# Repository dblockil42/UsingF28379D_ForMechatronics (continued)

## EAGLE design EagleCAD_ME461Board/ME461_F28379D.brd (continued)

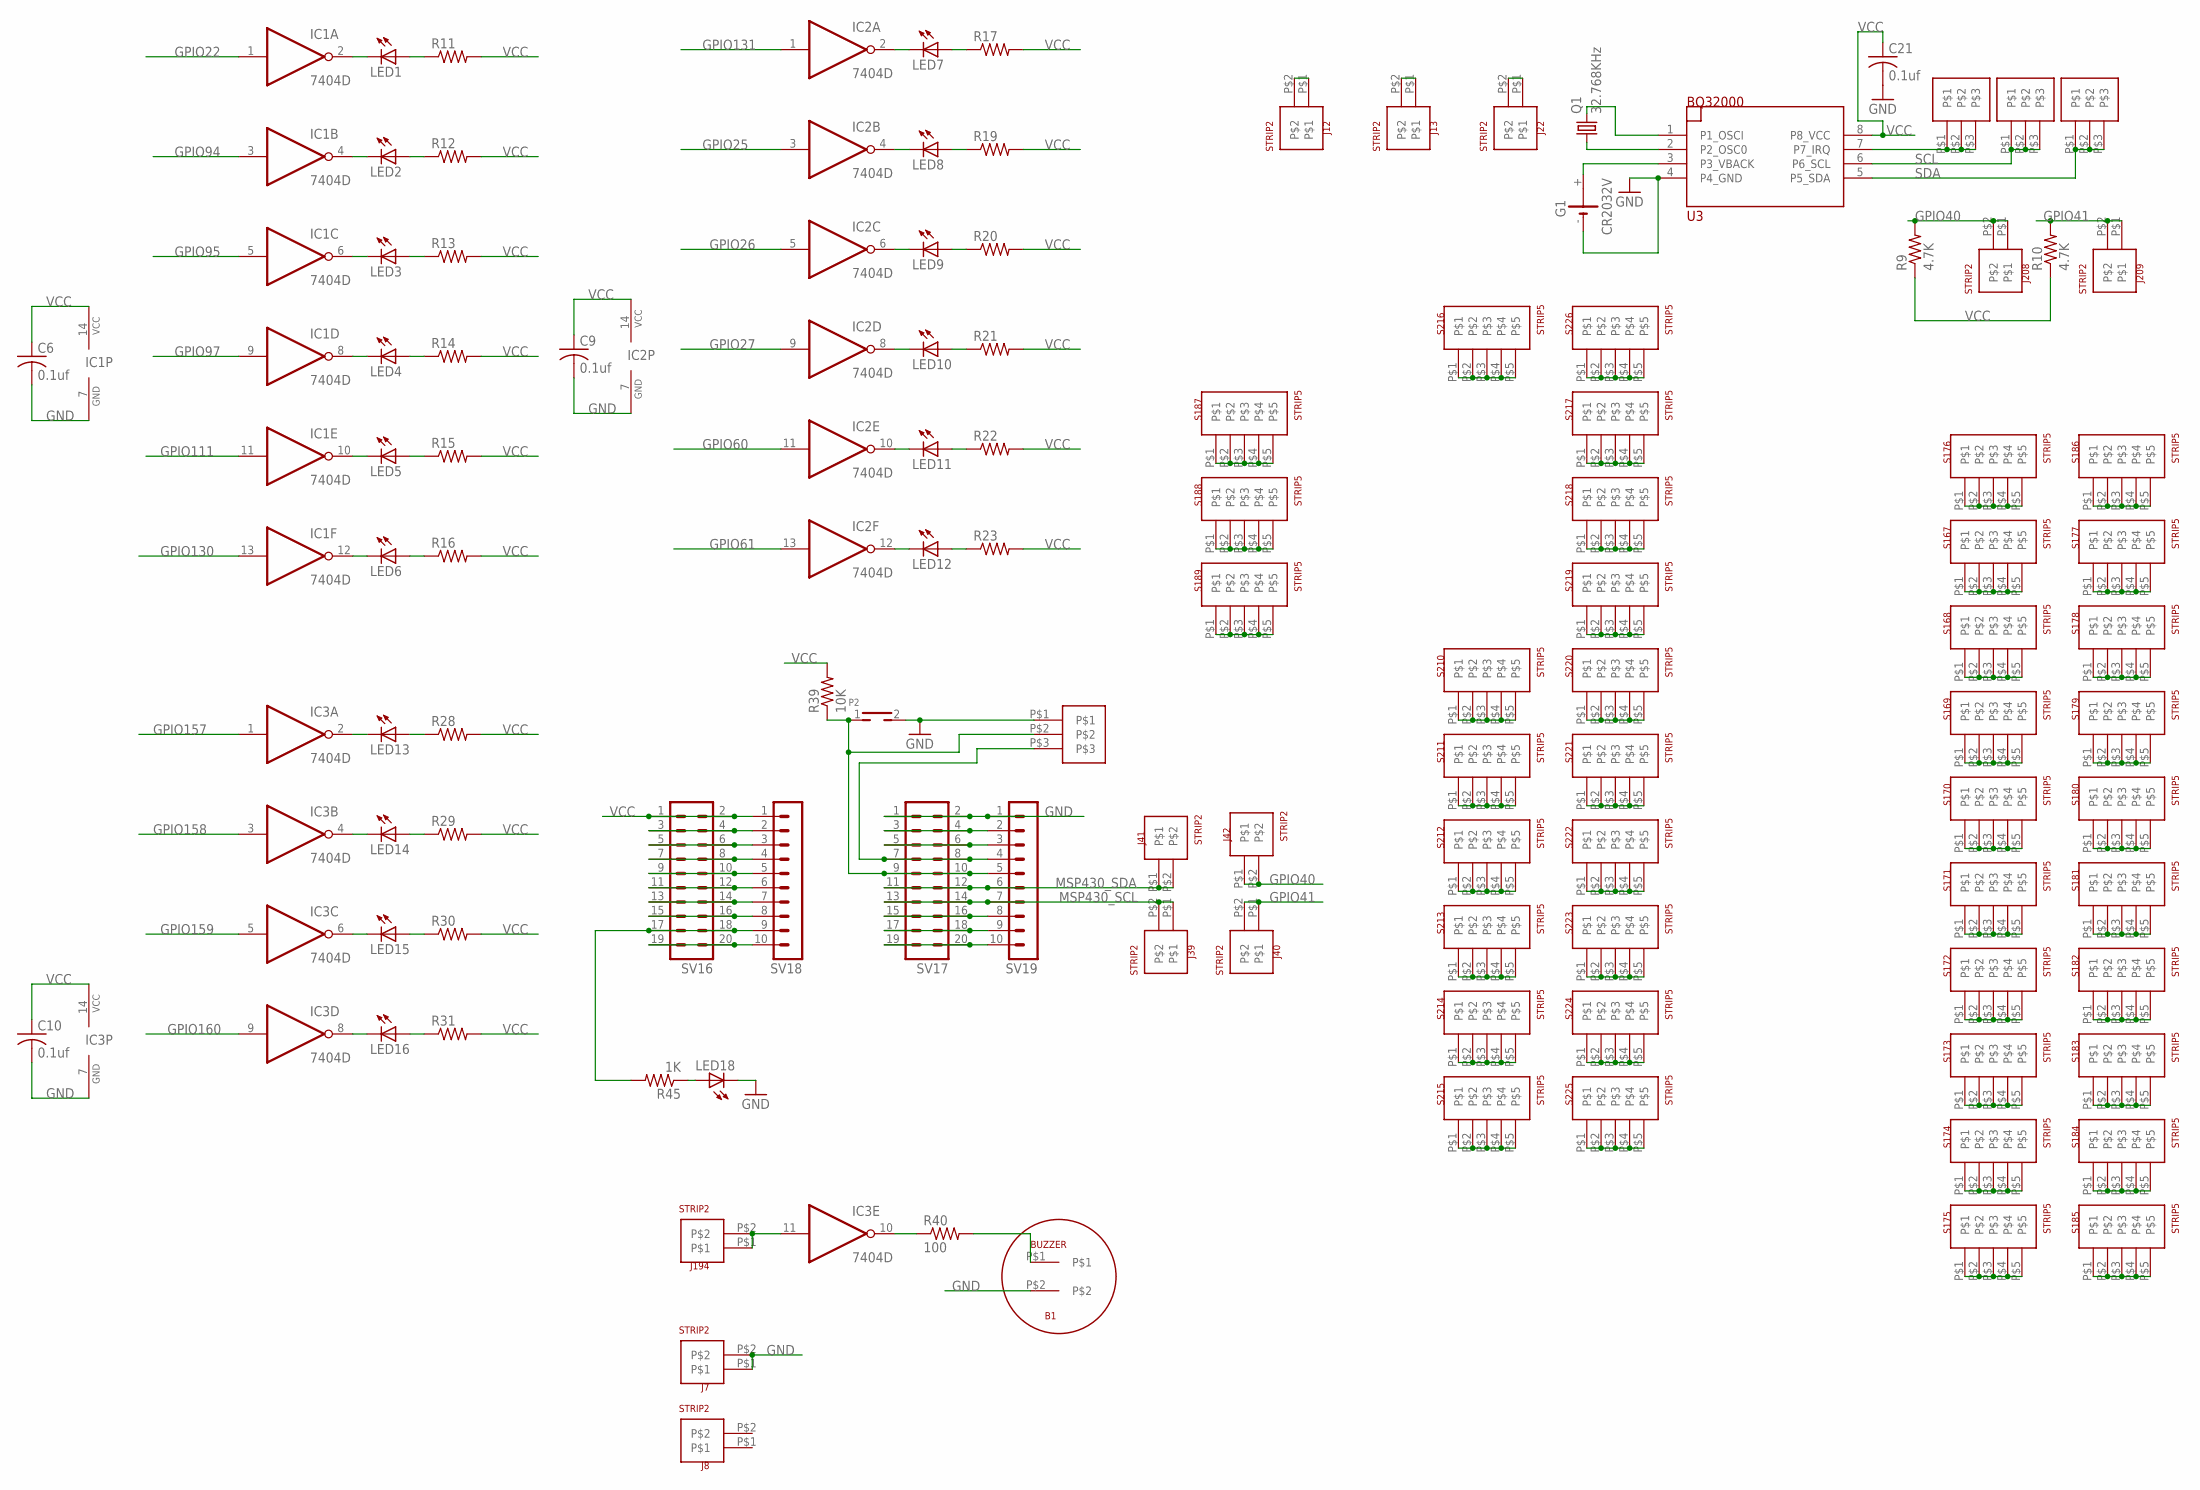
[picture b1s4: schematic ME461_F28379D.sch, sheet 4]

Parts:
B1: BUZZER
C6, C9, C10, C21: 0.1uf; C1206
G1: CR2032V
IC1, IC2, IC3: 7404D; SO14
J1, J2, J3, J43: STRIP3
J7, J8, J12, J13, J22, J39, J40, J41, J42, J194, J208, J209: STRIP2
LED1, LED2, LED3, LED4, LED5, LED6, LED7, LED8, LED9, LED10, LED11, LED12, LED13, LED14, LED15, LED16, LED18: LEDCHIPLED_1206; CHIPLED_1206
P2: TH_PUSHBOTTON; TH_PUSHBUTTON
Q1: 32.768KHz; TC26H
R9, R10: 4.7K; R1206
R11, R12, R13, R14, R15, R16, R17, R19, R20, R21, R22, R23, R28, R29, R30, R31: R-US_R1206; R1206
R39: 10K; R1206
R40: 100; R1206
R45: 1K; R1206
S167, S168, S169, S170, S171, S172, S173, S174, S175, S176, S177, S178, S179, S180, S181, S182, S183, S184, S185, S186, S187, S188, S189, S210, S211, S212, S213, S214, S215, S216, S217, S218, S219, S220, S221, S222, S223, S224, S225, S226: STRIP5
SV16, SV17: MA10-2
SV18, SV19: MA10-1
U3: BQ32000; SO08

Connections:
GND: B1.P$2, C6.2, C9.2, C10.2, C21.2, G1.-, IC1.7 (GND), IC2.7 (GND), IC3.7 (GND), J7.P$1, J7.P$2, J43.P$1, LED18.C, P2.2, SV17.1, SV17.2, SV19.1, U3.4 (P4_GND); also elsewhere on the board
GPIO22: IC1.1 (I); also elsewhere on the board
GPIO25: IC2.3 (I); also elsewhere on the board
GPIO26: IC2.5 (I); also elsewhere on the board
GPIO27: IC2.9 (I); also elsewhere on the board
GPIO40: J42.P$1, J42.P$2, J208.P$1, J208.P$2, R9.2; also elsewhere on the board
GPIO41: J40.P$1, J40.P$2, J209.P$1, J209.P$2, R10.2; also elsewhere on the board
GPIO60: IC2.11 (I); also elsewhere on the board
GPIO61: IC2.13 (I); also elsewhere on the board
GPIO94: IC1.3 (I); also elsewhere on the board
GPIO95: IC1.5 (I); also elsewhere on the board
GPIO97: IC1.9 (I); also elsewhere on the board
GPIO111: IC1.11 (I); also elsewhere on the board
GPIO130: IC1.13 (I); also elsewhere on the board
GPIO131: IC2.1 (I); also elsewhere on the board
GPIO157: IC3.1 (I); also elsewhere on the board
GPIO158: IC3.3 (I); also elsewhere on the board
GPIO159: IC3.5 (I); also elsewhere on the board
GPIO160: IC3.9 (I); also elsewhere on the board
MSP430_SCL: J39.P$1, J39.P$2, SV17.13, SV17.14, SV19.7
MSP430_SDA: J41.P$1, J41.P$2, SV17.11, SV17.12, SV19.6
unnamed: J12.P$1, J12.P$2
unnamed: J13.P$1, J13.P$2
unnamed: J22.P$1, J22.P$2
unnamed: R45.2, SV16.17, SV16.18, SV18.9
unnamed: SV16.3, SV16.4, SV18.2
unnamed: SV16.5, SV16.6, SV18.3
unnamed: SV16.7, SV16.8, SV18.4
unnamed: SV16.9, SV16.10, SV18.5
unnamed: SV16.11, SV16.12, SV18.6
unnamed: SV16.13, SV16.14, SV18.7
unnamed: SV16.15, SV16.16, SV18.8
unnamed: LED18.A, R45.1
unnamed: SV16.19, SV16.20, SV18.10
unnamed: SV17.3, SV17.4, SV19.2
unnamed: SV17.5, SV17.6, SV19.3
unnamed: J43.P$3, SV17.7, SV17.8, SV19.4
unnamed: SV17.15, SV17.16, SV19.8
unnamed: SV17.17, SV17.18, SV19.9
unnamed: SV17.19, SV17.20, SV19.10
unnamed: J43.P$2, P2.1, R39.1, SV17.9, SV17.10, SV19.5
unnamed: IC3.10 (O), R40.1
unnamed: B1.P$1, R40.2
unnamed: Q1.1, U3.2 (P2_OSC0)
unnamed: Q1.2, U3.1 (P1_OSCI)
unnamed: J1.P$1, J1.P$2, J1.P$3, U3.7 (P7_IRQ)
unnamed: G1.+, U3.3 (P3_VBACK)
unnamed: IC2.2 (O), LED7.C
unnamed: LED7.A, R17.1
unnamed: IC2.4 (O), LED8.C
unnamed: LED8.A, R19.1
unnamed: IC2.6 (O), LED9.C
unnamed: S167.P$1, S167.P$2, S167.P$3, S167.P$4, S167.P$5
unnamed: S168.P$1, S168.P$2, S168.P$3, S168.P$4, S168.P$5
unnamed: S169.P$1, S169.P$2, S169.P$3, S169.P$4, S169.P$5
unnamed: S170.P$1, S170.P$2, S170.P$3, S170.P$4, S170.P$5
unnamed: S171.P$1, S171.P$2, S171.P$3, S171.P$4, S171.P$5
unnamed: S172.P$1, S172.P$2, S172.P$3, S172.P$4, S172.P$5
unnamed: S173.P$1, S173.P$2, S173.P$3, S173.P$4, S173.P$5
unnamed: S174.P$1, S174.P$2, S174.P$3, S174.P$4, S174.P$5
unnamed: S175.P$1, S175.P$2, S175.P$3, S175.P$4, S175.P$5
unnamed: S176.P$1, S176.P$2, S176.P$3, S176.P$4, S176.P$5
unnamed: S177.P$1, S177.P$2, S177.P$3, S177.P$4, S177.P$5
unnamed: S178.P$1, S178.P$2, S178.P$3, S178.P$4, S178.P$5
unnamed: S179.P$1, S179.P$2, S179.P$3, S179.P$4, S179.P$5
unnamed: S180.P$1, S180.P$2, S180.P$3, S180.P$4, S180.P$5
unnamed: S181.P$1, S181.P$2, S181.P$3, S181.P$4, S181.P$5
unnamed: S182.P$1, S182.P$2, S182.P$3, S182.P$4, S182.P$5
unnamed: S183.P$1, S183.P$2, S183.P$3, S183.P$4, S183.P$5
unnamed: S184.P$1, S184.P$2, S184.P$3, S184.P$4, S184.P$5
unnamed: S185.P$1, S185.P$2, S185.P$3, S185.P$4, S185.P$5
unnamed: S186.P$1, S186.P$2, S186.P$3, S186.P$4, S186.P$5
unnamed: S187.P$1, S187.P$2, S187.P$3, S187.P$4, S187.P$5
unnamed: S188.P$1, S188.P$2, S188.P$3, S188.P$4, S188.P$5
unnamed: S189.P$1, S189.P$2, S189.P$3, S189.P$4, S189.P$5
unnamed: S210.P$1, S210.P$2, S210.P$3, S210.P$4, S210.P$5
unnamed: S211.P$1, S211.P$2, S211.P$3, S211.P$4, S211.P$5
unnamed: S212.P$1, S212.P$2, S212.P$3, S212.P$4, S212.P$5
unnamed: S213.P$1, S213.P$2, S213.P$3, S213.P$4, S213.P$5
unnamed: S214.P$1, S214.P$2, S214.P$3, S214.P$4, S214.P$5
unnamed: S215.P$1, S215.P$2, S215.P$3, S215.P$4, S215.P$5
unnamed: S216.P$1, S216.P$2, S216.P$3, S216.P$4, S216.P$5
unnamed: S217.P$1, S217.P$2, S217.P$3, S217.P$4, S217.P$5
unnamed: S218.P$1, S218.P$2, S218.P$3, S218.P$4, S218.P$5
unnamed: S219.P$1, S219.P$2, S219.P$3, S219.P$4, S219.P$5
unnamed: S220.P$1, S220.P$2, S220.P$3, S220.P$4, S220.P$5
unnamed: S221.P$1, S221.P$2, S221.P$3, S221.P$4, S221.P$5
unnamed: S222.P$1, S222.P$2, S222.P$3, S222.P$4, S222.P$5
unnamed: S223.P$1, S223.P$2, S223.P$3, S223.P$4, S223.P$5
unnamed: S224.P$1, S224.P$2, S224.P$3, S224.P$4, S224.P$5
unnamed: S225.P$1, S225.P$2, S225.P$3, S225.P$4, S225.P$5
unnamed: S226.P$1, S226.P$2, S226.P$3, S226.P$4, S226.P$5
unnamed: IC1.2 (O), LED1.C
unnamed: LED1.A, R11.1
unnamed: IC1.4 (O), LED2.C
unnamed: LED2.A, R12.1
unnamed: IC1.6 (O), LED3.C
unnamed: LED3.A, R13.1
unnamed: IC1.8 (O), LED4.C
unnamed: LED4.A, R14.1
unnamed: IC1.10 (O), LED5.C
unnamed: LED5.A, R15.1
unnamed: IC1.12 (O), LED6.C
unnamed: LED6.A, R16.1
unnamed: LED9.A, R20.1
unnamed: IC2.8 (O), LED10.C
unnamed: LED10.A, R21.1
unnamed: IC2.10 (O), LED11.C
unnamed: LED11.A, R22.1
unnamed: IC2.12 (O), LED12.C
unnamed: LED12.A, R23.1
unnamed: IC3.2 (O), LED13.C
unnamed: LED13.A, R28.1
unnamed: IC3.4 (O), LED14.C
unnamed: LED14.A, R29.1
unnamed: IC3.6 (O), LED15.C
unnamed: LED15.A, R30.1
unnamed: IC3.8 (O), LED16.C
unnamed: LED16.A, R31.1
unnamed: IC3.11 (I), J194.P$1, J194.P$2
SCL: J2.P$1, J2.P$2, J2.P$3, U3.6 (P6_SCL)
SDA: J3.P$1, J3.P$2, J3.P$3, U3.5 (P5_SDA)
VCC: C6.1, C9.1, C10.1, C21.1, IC1.14 (VCC), IC2.14 (VCC), IC3.14 (VCC), R9.1, R10.1, R11.2, R12.2, R13.2, R14.2, R15.2, R16.2, R17.2, R19.2, R20.2, R21.2, R22.2, R23.2, R28.2, R29.2, R30.2, R31.2, R39.2, SV16.1, SV16.2, SV18.1, U3.8 (P8_VCC); also elsewhere on the board

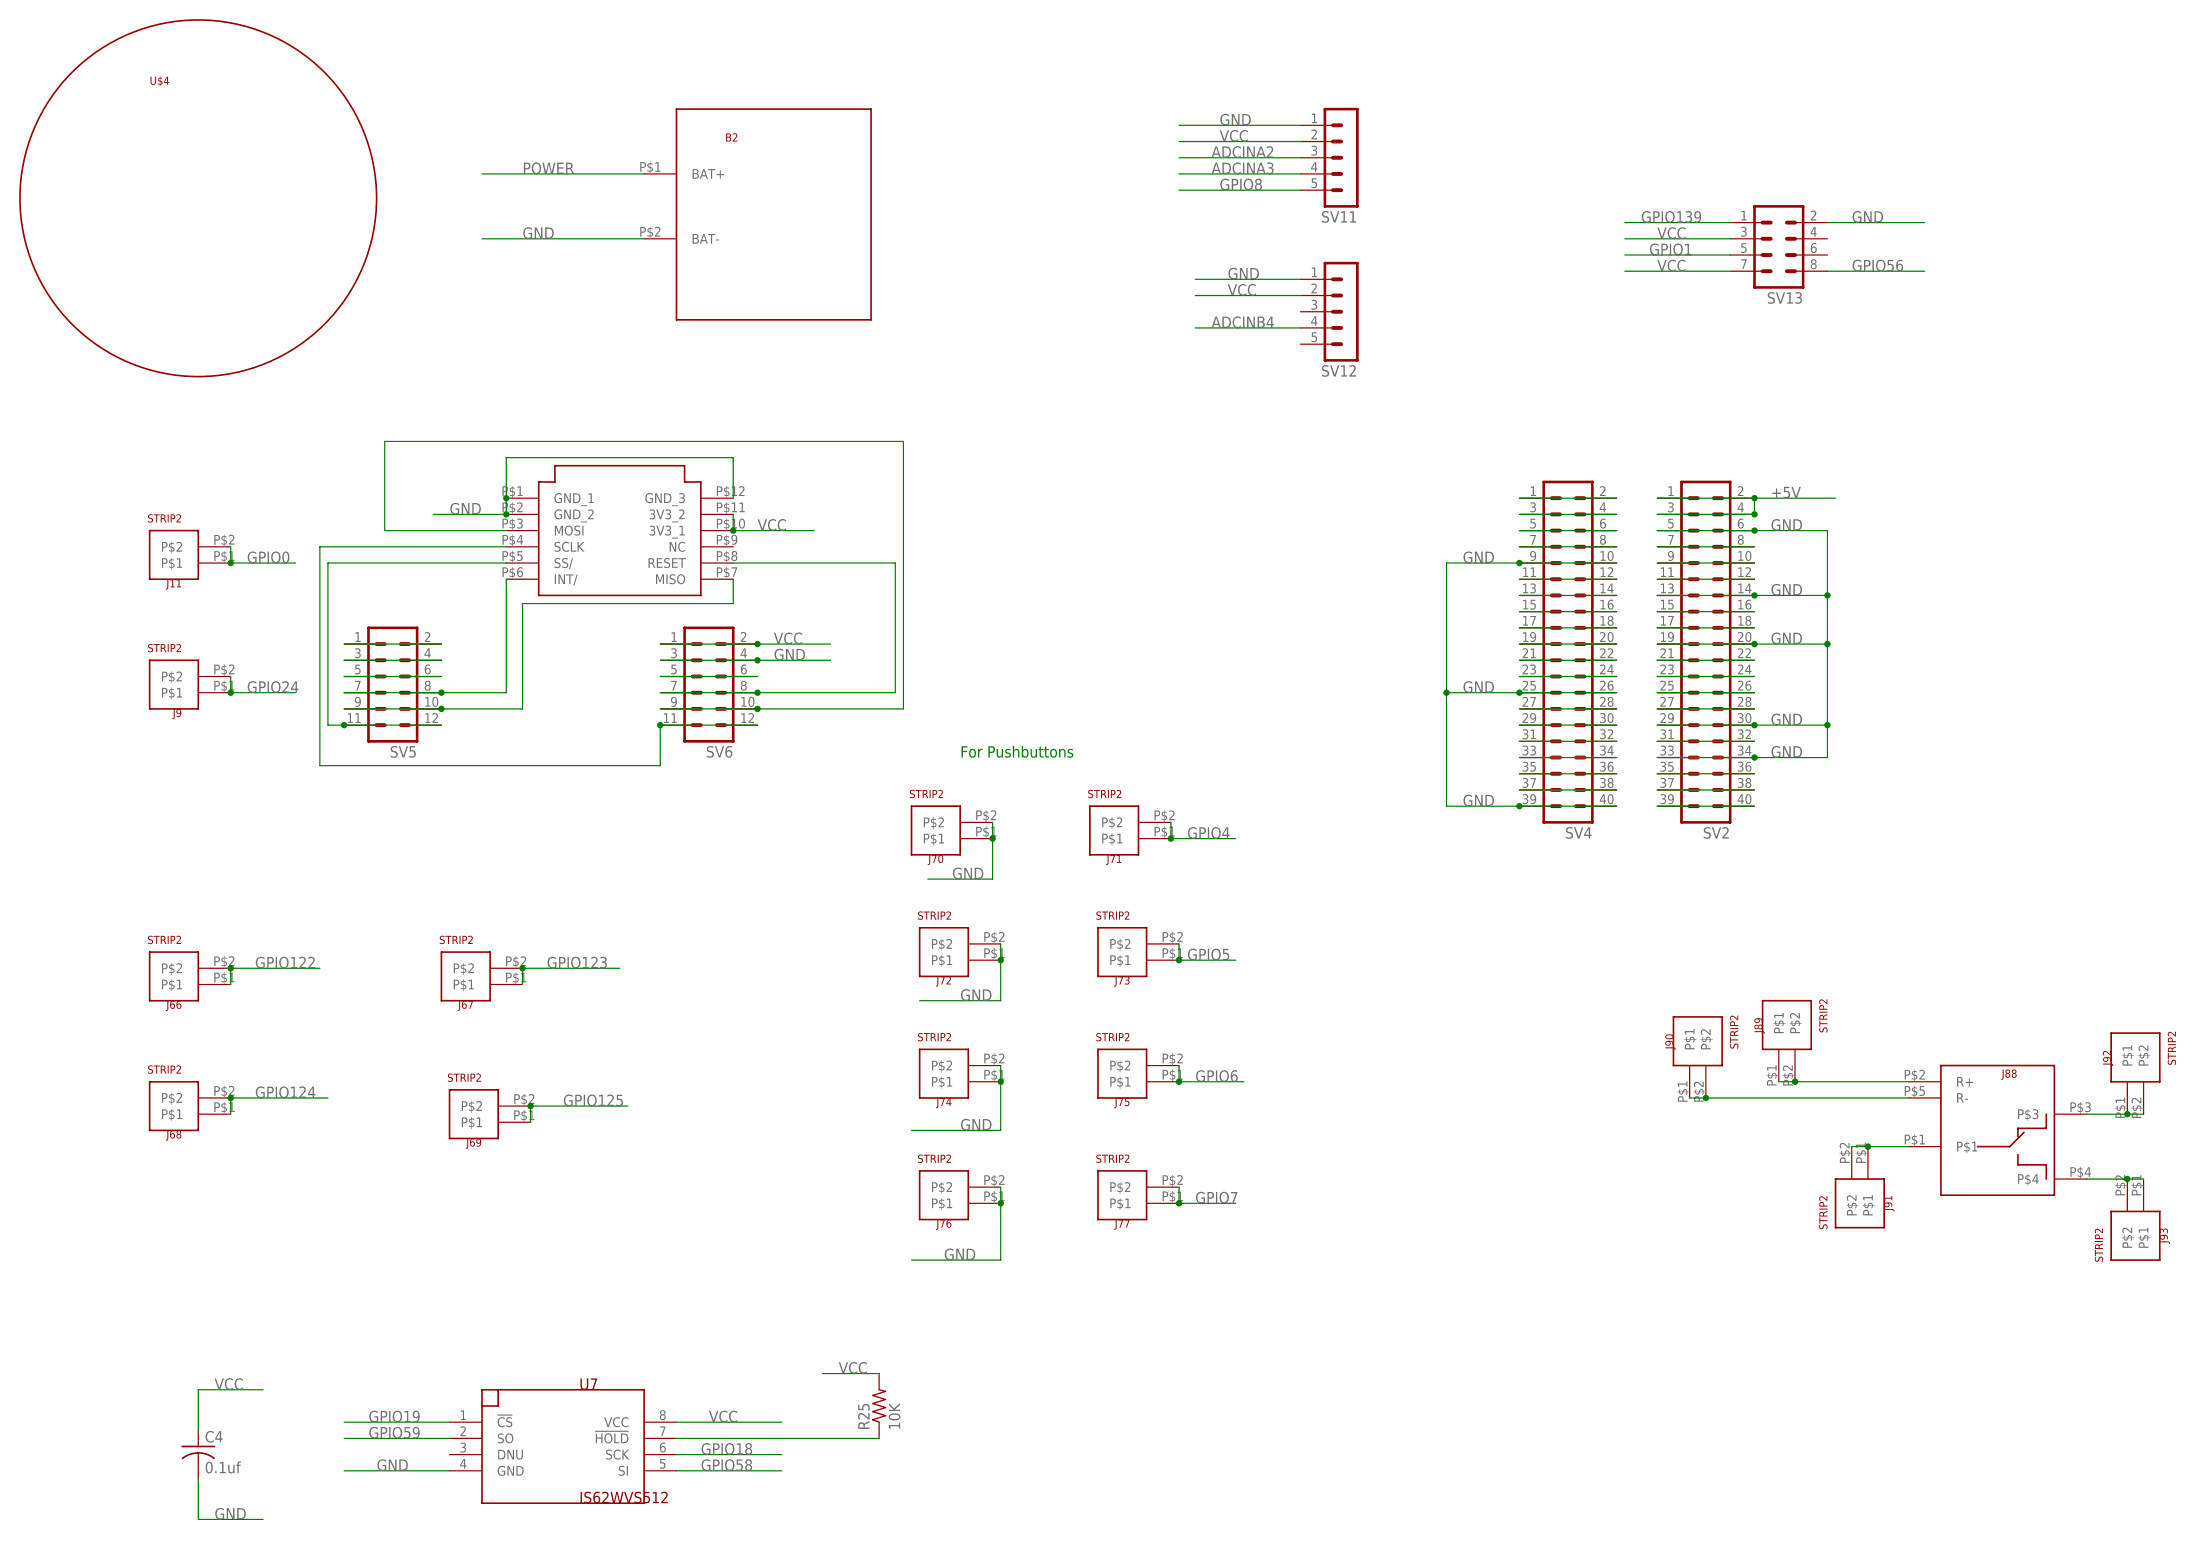
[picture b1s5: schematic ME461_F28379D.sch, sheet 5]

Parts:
B2: BATTERY_4AA_HOLDER
C4: 0.1uf; C1206
ETH1: USR_ES1_W5500
J9, J11, J66, J67, J68, J69, J70, J71, J72, J73, J74, J75, J76, J77, J89, J90, J91, J92, J93: STRIP2
J88: RELAY_JQC-3F_5V
R25: 10K; M1206
SV2, SV4: MA20-2
SV5, SV6: MA06-2
SV11, SV12: MA05-1
SV13: MA04-2
U7: IS62WVS512; SO08
U$4: CASTERWHEEL

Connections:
+5V: SV2.1, SV2.2, SV2.3, SV2.4; also elsewhere on the board
ADCINA2: SV11.3; also elsewhere on the board
ADCINA3: SV11.4; also elsewhere on the board
ADCINB4: SV12.4; also elsewhere on the board
GND: B2.P$2 (BAT-), C4.2, ETH1.P$1 (GND_1), ETH1.P$2 (GND_2), ETH1.P$12 (GND_3), J70.P$1, J70.P$2, J72.P$1, J72.P$2, J74.P$1, J74.P$2, J76.P$1, J76.P$2, SV2.5, SV2.6, SV2.13, SV2.14, SV2.19, SV2.20, SV2.29, SV2.30, SV2.33, SV2.34, SV4.9, SV4.10, SV4.25, SV4.26, SV4.39, SV4.40, SV6.3, SV6.4, SV11.1, SV12.1, SV13.2, U7.4 (GND); also elsewhere on the board
GPIO0: J11.P$1, J11.P$2; also elsewhere on the board
GPIO1: SV13.5; also elsewhere on the board
GPIO4: J71.P$1, J71.P$2; also elsewhere on the board
GPIO5: J73.P$1, J73.P$2; also elsewhere on the board
GPIO6: J75.P$1, J75.P$2; also elsewhere on the board
GPIO7: J77.P$1, J77.P$2; also elsewhere on the board
GPIO8: SV11.5; also elsewhere on the board
GPIO18: U7.6 (SCK); also elsewhere on the board
GPIO19: U7.1 (!CS); also elsewhere on the board
GPIO24: J9.P$1, J9.P$2; also elsewhere on the board
GPIO56: SV13.8; also elsewhere on the board
GPIO58: U7.5 (SI); also elsewhere on the board
GPIO59: U7.2 (SO); also elsewhere on the board
GPIO122: J66.P$1, J66.P$2; also elsewhere on the board
GPIO123: J67.P$1, J67.P$2; also elsewhere on the board
GPIO124: J68.P$1, J68.P$2; also elsewhere on the board
GPIO125: J69.P$1, J69.P$2; also elsewhere on the board
GPIO139: SV13.1; also elsewhere on the board
unnamed: R25.1, U7.7 (!HOLD)
unnamed: SV4.1, SV4.2
unnamed: SV5.1, SV5.2
unnamed: SV5.3, SV5.4
unnamed: SV5.5, SV5.6
unnamed: SV4.3, SV4.4
unnamed: SV4.5, SV4.6
unnamed: SV4.7, SV4.8
unnamed: ETH1.P$6 (INT/), SV5.7, SV5.8
unnamed: SV4.11, SV4.12
unnamed: SV4.13, SV4.14
unnamed: SV4.15, SV4.16
unnamed: SV4.17, SV4.18
unnamed: SV4.19, SV4.20
unnamed: SV4.21, SV4.22
unnamed: SV4.23, SV4.24
unnamed: ETH1.P$7 (MISO), SV5.9, SV5.10
unnamed: SV4.27, SV4.28
unnamed: SV4.29, SV4.30
unnamed: SV4.31, SV4.32
unnamed: SV4.33, SV4.34
unnamed: SV4.35, SV4.36
unnamed: SV4.37, SV4.38
unnamed: ETH1.P$5 (SS/), SV5.11, SV5.12
unnamed: SV2.39, SV2.40
unnamed: SV2.37, SV2.38
unnamed: SV2.35, SV2.36
unnamed: SV2.31, SV2.32
unnamed: SV2.27, SV2.28
unnamed: SV2.25, SV2.26
unnamed: SV2.23, SV2.24
unnamed: SV2.21, SV2.22
unnamed: SV6.5, SV6.6
unnamed: SV2.17, SV2.18
unnamed: SV2.15, SV2.16
unnamed: ETH1.P$8 (RESET), SV6.7, SV6.8
unnamed: SV2.11, SV2.12
unnamed: SV2.9, SV2.10
unnamed: SV2.7, SV2.8
unnamed: ETH1.P$3 (MOSI), SV6.9, SV6.10
unnamed: ETH1.P$4 (SCLK), SV6.11, SV6.12
unnamed: J88.P$2 (R+), J89.P$1, J89.P$2
unnamed: J88.P$5 (R-), J90.P$1, J90.P$2
unnamed: J88.P$1, J91.P$1, J91.P$2
unnamed: J88.P$3, J92.P$1, J92.P$2
unnamed: J88.P$4, J93.P$1, J93.P$2
POWER: B2.P$1 (BAT+); also elsewhere on the board
VCC: C4.1, ETH1.P$10 (3V3_1), ETH1.P$11 (3V3_2), R25.2, SV6.1, SV6.2, SV11.2, SV12.2, SV13.3, SV13.7, U7.8 (VCC); also elsewhere on the board

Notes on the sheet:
For Pushbuttons

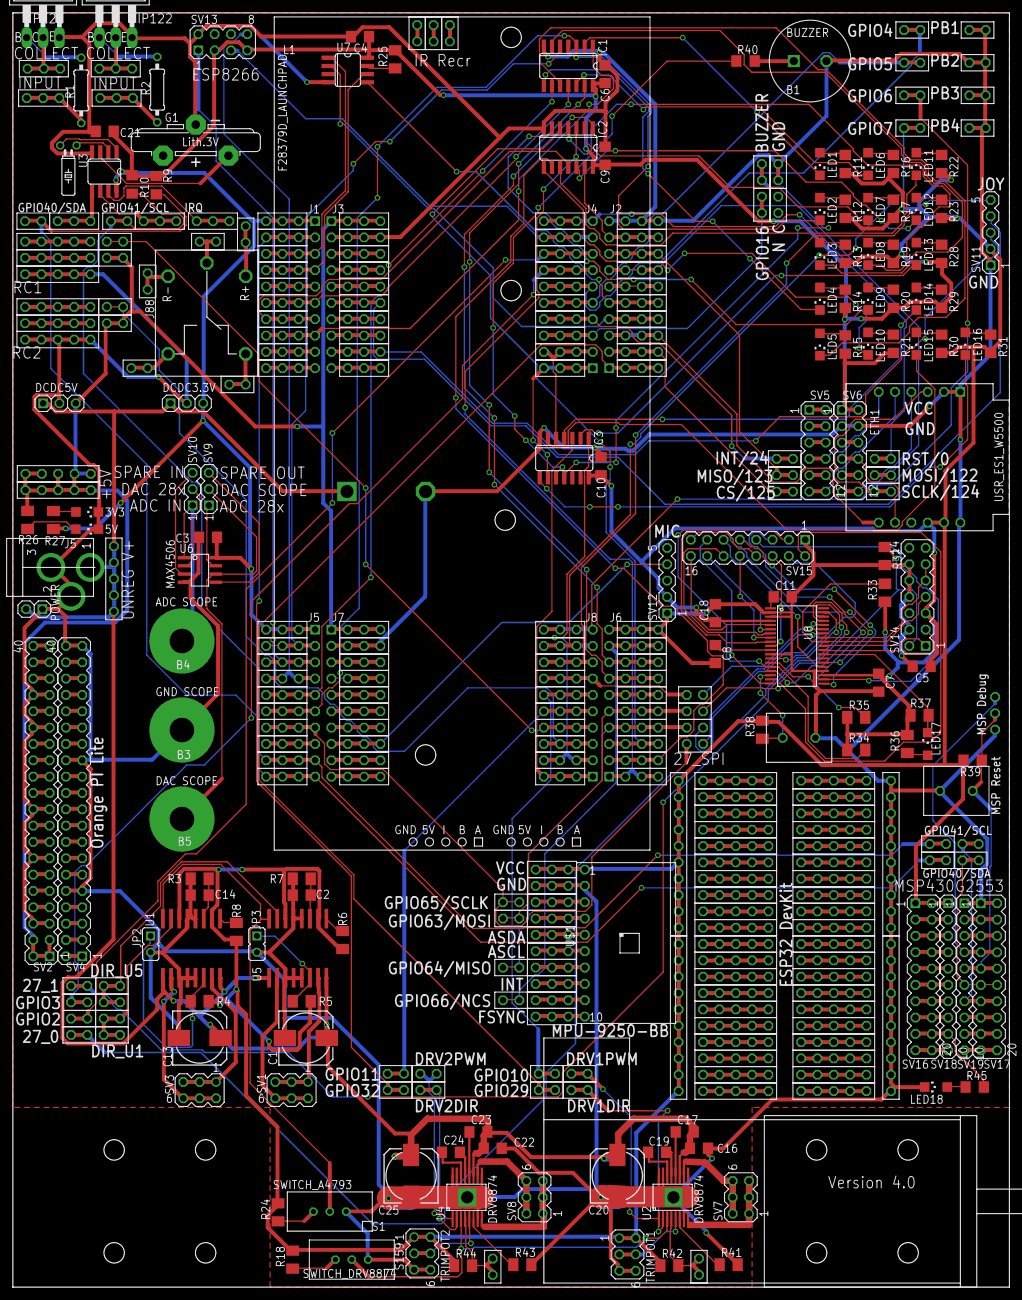
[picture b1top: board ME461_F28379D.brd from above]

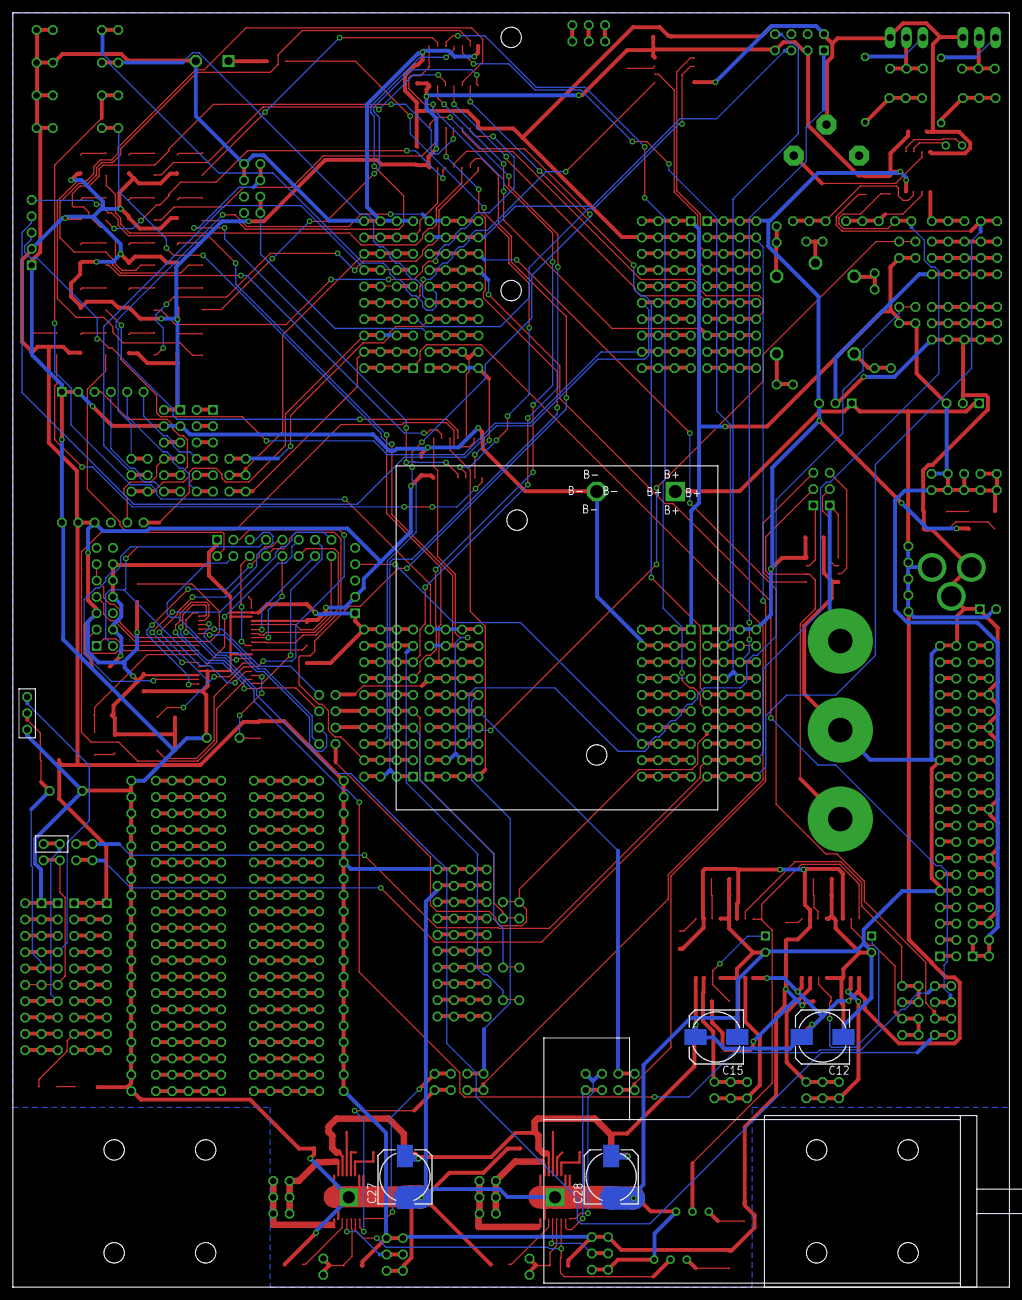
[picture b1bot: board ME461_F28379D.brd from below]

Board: 2 copper layers, 154.9 x 198.1 mm, 363 parts (8 on the bottom side), 318 nets.

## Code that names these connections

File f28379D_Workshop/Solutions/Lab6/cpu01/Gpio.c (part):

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	GpioCtrlRegs.GPACSEL4.all = 0x00000000;		// GPIO 24-31 /.

	//-----------------------------------------------------------------------------------------------------
	GpioCtrlRegs.GPAGMUX1.bit.GPIO0 = 0;		// 0|0=GPIO  0|1=EPWM1A       0|2=rsvd         0|3=rsvd
	GpioCtrlRegs.GPAMUX1.bit.GPIO0  = 1;		// 1|0=GPIO  1|1=rsvd         1|2=SDAA         1|3=rsvd
												// 2|0=GPIO  2|1=rsvd         2|2=rsvd         2|3=rsvd
												// 3|0=GPIO  3|1=rsvd         3|2=rsvd         3|3=rsvd
	//-----------------------------------------------------------------------------------------------------
	GpioCtrlRegs.GPAGMUX1.bit.GPIO1 = 0;		// 0|0=GPIO  0|1=EPWM1B       0|2=rsvd         0|3=MFSRB
	GpioCtrlRegs.GPAMUX1.bit.GPIO1  = 0;		// 1|0=GPIO  1|1=rsvd         1|2=SCLA         1|3=rsvd
												// 2|0=GPIO  2|1=rsvd         2|2=rsvd         2|3=rsvd
												// 3|0=GPIO  3|1=rsvd         3|2=rsvd         3|3=rsvd
	//-----------------------------------------------------------------------------------------------------
	GpioCtrlRegs.GPAGMUX1.bit.GPIO2 = 0;		// 0|0=GPIO  0|1=EPWM2A       0|2=rsvd         0|3=rsvd
	GpioCtrlRegs.GPAMUX1.bit.GPIO2  = 0;		// 1|0=GPIO  1|1=OUTPUTXBAR1  1|2=SDAB         1|3=rsvd
												// 2|0=GPIO  2|1=rsvd         2|2=rsvd         2|3=rsvd
												// 3|0=GPIO  3|1=rsvd         3|2=rsvd         3|3=rsvd
	//-----------------------------------------------------------------------------------------------------
	GpioCtrlRegs.GPAGMUX1.bit.GPIO3 = 0;		// 0|0=GPIO  0|1=EPWM2B       0|2=OUTPUTXBAR2  0|3=MCLKRB
	GpioCtrlRegs.GPAMUX1.bit.GPIO3  = 0;		// 1|0=GPIO  1|1=OUTPUTXBAR2  1|2=SCLB         1|3=rsvd
												// 2|0=GPIO  2|1=rsvd         2|2=rsvd         2|3=rsvd
												// 3|0=GPIO  3|1=rsvd         3|2=rsvd         3|3=rsvd
	//-----------------------------------------------------------------------------------------------------
	GpioCtrlRegs.GPAGMUX1.bit.GPIO4 = 0;		// 0|0=GPIO  0|1=EPWM3A       0|2=rsvd         0|3=rsvd
	GpioCtrlRegs.GPAMUX1.bit.GPIO4  = 0;		// 1|0=GPIO  1|1=OUTPUTXBAR3  1|2=CANTXA       1|3=rsvd
												// 2|0=GPIO  2|1=rsvd         2|2=rsvd         2|3=rsvd
												// 3|0=GPIO  3|1=rsvd         3|2=rsvd         3|3=rsvd
	//-----------------------------------------------------------------------------------------------------
	GpioCtrlRegs.GPAGMUX1.bit.GPIO5 = 0;		// 0|0=GPIO  0|1=EPWM3B       0|2=MFSRA        0|3=OUTPUTXBAR3
	GpioCtrlRegs.GPAMUX1.bit.GPIO5  = 0;		// 1|0=GPIO  1|1=rsvd         1|2=CANRXA       1|3=rsvd
												// 2|0=GPIO  2|1=rsvd         2|2=rsvd         2|3=rsvd
												// 3|0=GPIO  3|1=rsvd         3|2=rsvd         3|3=rsvd
	//-----------------------------------------------------------------------------------------------------
	GpioCtrlRegs.GPAGMUX1.bit.GPIO6 = 0;		// 0|0=GPIO  0|1=EPWM4A       0|2=OUTPUTXBAR4  0|3=EPWMSYNCO
	GpioCtrlRegs.GPAMUX1.bit.GPIO6  = 0;		// 1|0=GPIO  1|1=EQEP3A       1|2=CANTXB       1|3=rsvd
												// 2|0=GPIO  2|1=rsvd         2|2=rsvd         2|3=rsvd
												// 3|0=GPIO  3|1=rsvd         3|2=rsvd         3|3=rsvd
	//-----------------------------------------------------------------------------------------------------
	GpioCtrlRegs.GPAGMUX1.bit.GPIO7 = 0;		// 0|0=GPIO  0|1=EPWM4B       0|2=MCLKRA       0|3=OUTPUTXBAR5
	GpioCtrlRegs.GPAMUX1.bit.GPIO7  = 0;		// 1|0=GPIO  1|1=EQEP3B       1|2=CANRXB       1|3=rsvd
												// 2|0=GPIO  2|1=rsvd         2|2=rsvd         2|3=rsvd
												// 3|0=GPIO  3|1=rsvd         3|2=rsvd         3|3=rsvd
	//-----------------------------------------------------------------------------------------------------
	GpioCtrlRegs.GPAGMUX1.bit.GPIO8 = 0;		// 0|0=GPIO  0|1=EPWM5A       0|2=CANTXB       0|3=ADCSOCAO
	GpioCtrlRegs.GPAMUX1.bit.GPIO8  = 0;		// 1|0=GPIO  1|1=EQEP3S       1|2=SCITXDA      1|3=rsvd
												// 2|0=GPIO  2|1=rsvd         2|2=rsvd         2|3=rsvd
												// 3|0=GPIO  3|1=rsvd         3|2=rsvd         3|3=rsvd
	//-----------------------------------------------------------------------------------------------------
	GpioCtrlRegs.GPAGMUX1.bit.GPIO9 = 0;		// 0|0=GPIO  0|1=EPWM5B       0|2=SCITXDB      0|3=OUTPUTXBAR6
	GpioCtrlRegs.GPAMUX1.bit.GPIO9  = 0;		// 1|0=GPIO  1|1=EQEP3I       1|2=SCIRXDA      1|3=rsvd
												// 2|0=GPIO  2|1=rsvd         2|2=rsvd         2|3=rsvd
												// 3|0=GPIO  3|1=rsvd         3|2=rsvd         3|3=rsvd
	//-----------------------------------------------------------------------------------------------------
	GpioCtrlRegs.GPAGMUX1.bit.GPIO10 = 0;		// 0|0=GPIO  0|1=EPWM6A       0|2=CANRXB       0|3=ADCSOCBO
	GpioCtrlRegs.GPAMUX1.bit.GPIO10  = 0;		// 1|0=GPIO  1|1=EQEP1A       1|2=SCITXDB      1|3=rsvd
												// 2|0=GPIO  2|1=rsvd         2|2=rsvd         2|3=rsvd
												// 3|0=GPIO  3|1=rsvd         3|2=rsvd         3|3=UPP-WAIT
	//-----------------------------------------------------------------------------------------------------
	GpioCtrlRegs.GPAGMUX1.bit.GPIO11 = 0;		// 0|0=GPIO  0|1=EPWM6B       0|2=SCIRXDB      0|3=OUTPUTXBAR7
	GpioCtrlRegs.GPAMUX1.bit.GPIO11  = 0;		// 1|0=GPIO  1|1=EQEP1B       1|2=SCIRXDB      1|3=rsvd
												// 2|0=GPIO  2|1=rsvd         2|2=rsvd         2|3=rsvd
												// 3|0=GPIO  3|1=rsvd         3|2=rsvd         3|3=UPP-STRT
	//-----------------------------------------------------------------------------------------------------
	GpioCtrlRegs.GPAGMUX1.bit.GPIO12 = 0;		// 0|0=GPIO  0|1=EPWM7A       0|2=CANTXB       0|3=MDXB
	GpioCtrlRegs.GPAMUX1.bit.GPIO12  = 0;		// 1|0=GPIO  1|1=EQEP1S       1|2=SCITXDC      1|3=rsvd
												// 2|0=GPIO  2|1=rsvd         2|2=rsvd         2|3=rsvd
												// 3|0=GPIO  3|1=rsvd         3|2=rsvd         3|3=UPP-ENA
	//-----------------------------------------------------------------------------------------------------
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												// 2|0=GPIO  2|1=rsvd         2|2=rsvd         2|3=rsvd
												// 3|0=GPIO  3|1=rsvd         3|2=rsvd         3|3=UPP-D7
	//-----------------------------------------------------------------------------------------------------
	GpioCtrlRegs.GPAGMUX1.bit.GPIO14 = 0;		// 0|0=GPIO  0|1=EPWM8A       0|2=SCITXDB      0|3=MCLKXB
	GpioCtrlRegs.GPAMUX1.bit.GPIO14  = 0;		// 1|0=GPIO  1|1=rsvd         1|2=OUTPUTXBAR3  1|3=rsvd
												// 2|0=GPIO  2|1=rsvd         2|2=rsvd         2|3=rsvd
												// 3|0=GPIO  3|1=rsvd         3|2=rsvd         3|3=UPP-D6
	//-----------------------------------------------------------------------------------------------------
	GpioCtrlRegs.GPAGMUX1.bit.GPIO15 = 0;		// 0|0=GPIO  0|1=EPWM8B       0|2=SCIRXDB      0|3=MFSXB
	GpioCtrlRegs.GPAMUX1.bit.GPIO15  = 0;		// 1|0=GPIO  1|1=rsvd         1|2=OUTPUTXBAR4  1|3=rsvd
												// 2|0=GPIO  2|1=rsvd         2|2=rsvd         2|3=rsvd
												// 3|0=GPIO  3|1=rsvd         3|2=rsvd         3|3=UPP-D5
	//-----------------------------------------------------------------------------------------------------
	GpioCtrlRegs.GPAGMUX2.bit.GPIO16 = 0;		// 0|0=GPIO  0|1=SPISIMOA     0|2=CANTXB       0|3=OUTPUTXBAR7
	GpioCtrlRegs.GPAMUX2.bit.GPIO16  = 0;		// 1|0=GPIO  1|1=EPWM9A       1|2=rsvd         1|3=SD1_D1
												// 2|0=GPIO  2|1=rsvd         2|2=rsvd         2|3=rsvd
												// 3|0=GPIO  3|1=rsvd         3|2=rsvd         3|3=UPP-D4
	//-----------------------------------------------------------------------------------------------------
	GpioCtrlRegs.GPAGMUX2.bit.GPIO17 = 0;		// 0|0=GPIO  0|1=SPISOMIA     0|2=CANRXB       0|3=OUTPUTXBAR8
	GpioCtrlRegs.GPAMUX2.bit.GPIO17  = 0;		// 1|0=GPIO  1|1=EPWM9B       1|2=rsvd         1|3=SD1_C1
												// 2|0=GPIO  2|1=rsvd         2|2=rsvd         2|3=rsvd
												// 3|0=GPIO  3|1=rsvd         3|2=rsvd         3|3=UPP-D3
	//-----------------------------------------------------------------------------------------------------
	GpioCtrlRegs.GPAGMUX2.bit.GPIO18 = 0;		// 0|0=GPIO  0|1=SPICLKA      0|2=SCITXDB      0|3=CANRXA
	GpioCtrlRegs.GPAMUX2.bit.GPIO18  = 0;		// 1|0=GPIO  1|1=EPWM10A      1|2=rsvd         1|3=SD1_D2
												// 2|0=GPIO  2|1=rsvd         2|2=rsvd         2|3=rsvd
												// 3|0=GPIO  3|1=rsvd         3|2=rsvd         3|3=UPP-D2
	//-----------------------------------------------------------------------------------------------------
	GpioCtrlRegs.GPAGMUX2.bit.GPIO19 = 0;		// 0|0=GPIO  0|1=SPISTEAn     0|2=SCIRXDB      0|3=CANTXA
	GpioCtrlRegs.GPAMUX2.bit.GPIO19  = 0;		// 1|0=GPIO  1|1=EPWM10B      1|2=rsvd         1|3=SD1_C2
												// 2|0=GPIO  2|1=rsvd         2|2=rsvd         2|3=rsvd
												// 3|0=GPIO  3|1=rsvd         3|2=rsvd         3|3=UPP-D1
	//-----------------------------------------------------------------------------------------------------
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												// 2|0=GPIO  2|1=rsvd         2|2=rsvd         2|3=rsvd
												// 3|0=GPIO  3|1=rsvd         3|2=rsvd         3|3=UPP-CLK
	//-----------------------------------------------------------------------------------------------------
	GpioCtrlRegs.GPAGMUX2.bit.GPIO22 = 0;		// 0|0=GPIO  0|1=EQEP1S       0|2=MCLKXA       0|3=SCITXDB
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
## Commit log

2022-08-14 Made first changes to README.md
2022-08-14 README.md changes
2022-08-14 Added Breakout board schematic
2022-08-14 Add Segbot Picture
2022-08-14 Type O
2022-08-14 First commit of Code
2022-08-15 Readme documentation additions
2022-08-15 readme additions
2022-09-05 Changed Youtube Playlist website
2024-12-23 Added labtest
